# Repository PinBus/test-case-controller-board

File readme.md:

# Test-case Controller Board - Rev. 1.0

This board has been developed to control demo setups. It is essentially a smaller sized pinball machine controller. This board is based on the Arduino Uno, paired with a PCA9685 breakout board, eight MOSFETs and a four by four input matrix.

You will need to have a stencil made to make this board yourself. The SMD part footprints are not made for hand soldering.

**Warning: These designs are made as part of a hobby project and thus come with no guarantees. Do not use these designs in for any critical systems! Working with voltages higher than +40V can be potentially dangerous, please take appropriate safety measures!**

## Optional parts

 - Connectors **J2** and **J3** are optional. These headers expose the I2C bus and UART respectively.
 - Connectors **J4**, **J5**, and **J6** are optional. These headers expose the microcontroller pins.
 - Connector **J7** or **J8** are optional. These connectors are connected to the +5V rail. You will need at least one to power the board. The other connector can be used to power another board.
 - Connector **J9** or **J10** are optional. These connectors are connected to the +48V rail. You will need at least one when using the MOSFETs. The other connector can be used to power another board.
 - MOSFETs **Q1** thru **Q8** are optional:
   - Do not populate **R4**, **R6**, connector **SOL0**, and **D3** when not using **Q1**;
   - Do not populate **R8**, **R10**, connector **SOL1**, and **D4** when not using **Q2**;
   - Do not populate **R5**, **R7**, connector **SOL2**, and **D5** when not using **Q3**;
   - Do not populate **R9**, **R11**, connector **SOL3**, and **D6** when not using **Q4**;
   - Do not populate **R12**, **R14**, connector **SOL4**, and **D7** when not using **Q5**;
   - Do not populate **R16**, **R18**, connector **SOL5**, and **D8** when not using **Q6**;
   - Do not populate **R13**, **R15**, connector **SOL6**, and **D9** when not using **Q7**;
   - Do not populate **R17**, **R19**, connector **SOL7**, and **D10** when not using **Q8**;
 - When not using a MOSFET, you can use its pin on the PCA9685 to drive an LED:
   - Populate **LED0** if **Q1** is not used;
   - Populate **LED1** if **Q2** is not used;
   - Populate **LED2** if **Q3** is not used;
   - Populate **LED3** if **Q4** is not used;
   - Populate **LED4** if **Q5** is not used;
   - Populate **LED5** if **Q6** is not used;
   - Populate **LED6** if **Q7** is not used;
   - Populate **LED7** if **Q8** is not used;
 - **SOL0** and **SOL2** can be populated with either a 2 pin or a 3 pin connector:
   - Do not populate **SOL1** when **SOL0** is populated with a 3 pin connector;
   - Do not populate **SOL3** when **SOL2** is populated with a 3 pin connector;
 - All connectors and diodes making up the input matrix are optional:
   - Bridge **JP3** thru **JP6** to enable columns;
   - Bridge **JP7** thru **JP10** to enable rows;
 - Capacitors **C6** thru **C9** are optional. Populating **C6** is recommended. Populate others if needed.
 - Capacitors **C10** thru **C13** are optional. Populate if needed.

## BOM

| Identifiers                        | Quantity | Part number         | Manufacturer              | Footprint   | Description |
| ---------------------------------- | -------: | ------------------- | ------------------------- | ----------- | ----------- |
| C1                                 |       1x | CL10A475KQ8NNWC     | Samsung Electro-Mechanics | 0603        | Capacitor, MLCC, 4.7μF, 10V |
| C2, C3, C4, C5                     |       4x | GRM188R60J476ME15J  | Murata Electronics        | 0603        | Capacitor, MLCC, 47μF, 6.3V |
| C6, C7, C8, C9                     |       4x | URS1A470MDD1TA      | Nichicon                  | ⌀5mm / 2mm  | Capacitor, Electrolytic, 47μ, 10V |
| C10, C11, C12, C13                 |       4x | UVZ1J101MPD         | Nichicon                  | ⌀10mm / 5mm | Capacitor, Electrolytic, 100μF, 63V |
| C14                                |       1x | LMK107BBJ106MALT    | Taiyo Yuden               | 0603        | Capacitor, MLCC, 10μF, 10V |
| D1                                 |       1x | 150060RS75000       | Wurth Elektronik          | 0603        | LED, Red |
| D2                                 |       1x | 150060GS75000       | Wurth Elektronik          | 0603        | LED, Green |
| D3, D4, D5, D6, D7, D8, D9, D10    |       8x | S1M-13-F            | Diodes Incorporated       | SMA         | Diode, rectifier, 1A, 1000V |
| D11, D12, D13, D14, D15, D16, D17, D18, D19, D20, D21, D22, D23, D24, D25, D26 |      16x | 1N4148W-G3-08       | Vishay / Dale             | SOD-123     | Diode, general purpose, 150mA, 100V |
| J1                                 |       1x |                     |                           | 2.54mm      | Connector, 2x3, Pin header |
| J2, J3                             |       2x | B4B-XH-A(LF)(SN)    | JST                       | 2.50mm      | Connector, 1x4 |
| J4, J5                             |       2x |                     |                           | 2.54mm      | Connector, 1x8, pin header |
| J6                                 |       1x |                     |                           | 2.54mm      | Connector, 1x6, pin header |
| J7, J8, LED0, LED1, LED2, LED3, LED4, LED5, LED6, LED7, LED8, LED9, LED10, LED11, LED12, LED13, LED14, LED15, MTX-0x0, MTX-0x1, MTX-0x2, MTX-0x3, MTX-1x0, MTX-1x1, MTX-1x2, MTX-1x3, MTX-2x0, MTX-2x1, MTX-2x2, MTX-2x3, MTX-3x0, MTX-3x1, MTX-3x2, MTX-3x3 |      34x | B2B-XH-A(LF)(SN)    | JST                       | 2.50mm      | Connector, 1x2 |
| J9, J10, SOL0, SOL1, SOL2, SOL3, SOL4, SOL5, SOL6, SOL7 |      10x | B2P-VH _or_ 1-1123723-3 | JST _or_ TE Connectivity | 3.96mm      | Connector, 1x2 |
| JP1, JP2                           |       2x |                     |                           | 2.54mm      | Jumper wire |
| SOL0, SOL2                         |       2x | B3P-VH _or_ 1-1123723-2 | JST _or_ TE Connectivity | 3.96mm      | Connector, 1x3 |
| Q1, Q2, Q3, Q4, Q5, Q6, Q7, Q8     |       8x | IRL540NPBF          | Infineon / IR             | TO-220      | MOSFET, 100V, 36A |
| R1                                 |       1x | CRCW06034K70JNEAC   | Vishay / Dale             | 0603        | Resistor, 4.7kΩ |
| R2, R3                             |       2x | CRCW06031K00FKEAC   | Vishay / Dale             | 0603        | Resistor, 1kΩ |
| R4, R5, R8, R9, R12, R13, R16, R17 |       8x | CRCW060310R0FKEAC   | Vishay / Dale             | 0603        | Resistor, 10Ω |
| R6, R7, R10, R11, R14, R15, R18, R19, R20, R21, R22, R23, R24, R25, R26, R27, R28, R29, R30, R31, R32 |      21x | CRCW060310K0JNEAC   | Vishay / Dale             | 0603        | Resistor, 10kΩ |
| SW1                                |       1x | PTS810SJM250SMTRLFS | C&K                       | -           | Switch |
| U1                                 |       1x | ATmega328P-AU       | Microchip Technology      | TQFP-32     | Microcontroller |
| U2                                 |       1x | PCA9685PW,112       | NXP Semiconductors        | TSSOP-28    | PWM driver |
| Y1                                 |       1x | CSTNE16M0V53L00ZR0  | Murata Electronics        | -           | Resonator, 16MHz, 15pF |

### Pin headers

You can use either the [JST VH series](https://www.jst-mfg.com/product/detail_e.php?series=262) pin headers or the TE Connectivity Economy Power series pin headers. These pin headers are known to fit, other 3.96mm pin pitch pin headers might also fit.

 - Order the JST SVH-21T-P1.1 crimp contacts (0.34mm² - 0.75mm²) for use with the JST pin headers
 - Order JST VHR-2N connector housing for the JST B2P-VH pin header
 - Order JST VHR-3N connector housing for the JST B3P-VH pin header
 - Order the [TE Connectivity 1123721-2](https://www.te.com/usa-en/product-1123721-2.html) crimp contacts (0.34mm² - 0.75mm²) for use with the TE Connectivity pin headers
 - Order the [TE Connectivity 1-1123722-2](https://www.te.com/usa-en/product-1-1123722-2.html) connector housing for the [TE Connectivity 1-1123723-2](https://www.te.com/usa-en/product-1-1123723-2.html) pin header
 - Order the [TE Connectivity 1-1123722-3](https://www.te.com/usa-en/product-1-1123722-3.html) connector housing for the [TE Connectivity 1-1123723-3](https://www.te.com/usa-en/product-1-1123723-3.html) pin header

## Pictures

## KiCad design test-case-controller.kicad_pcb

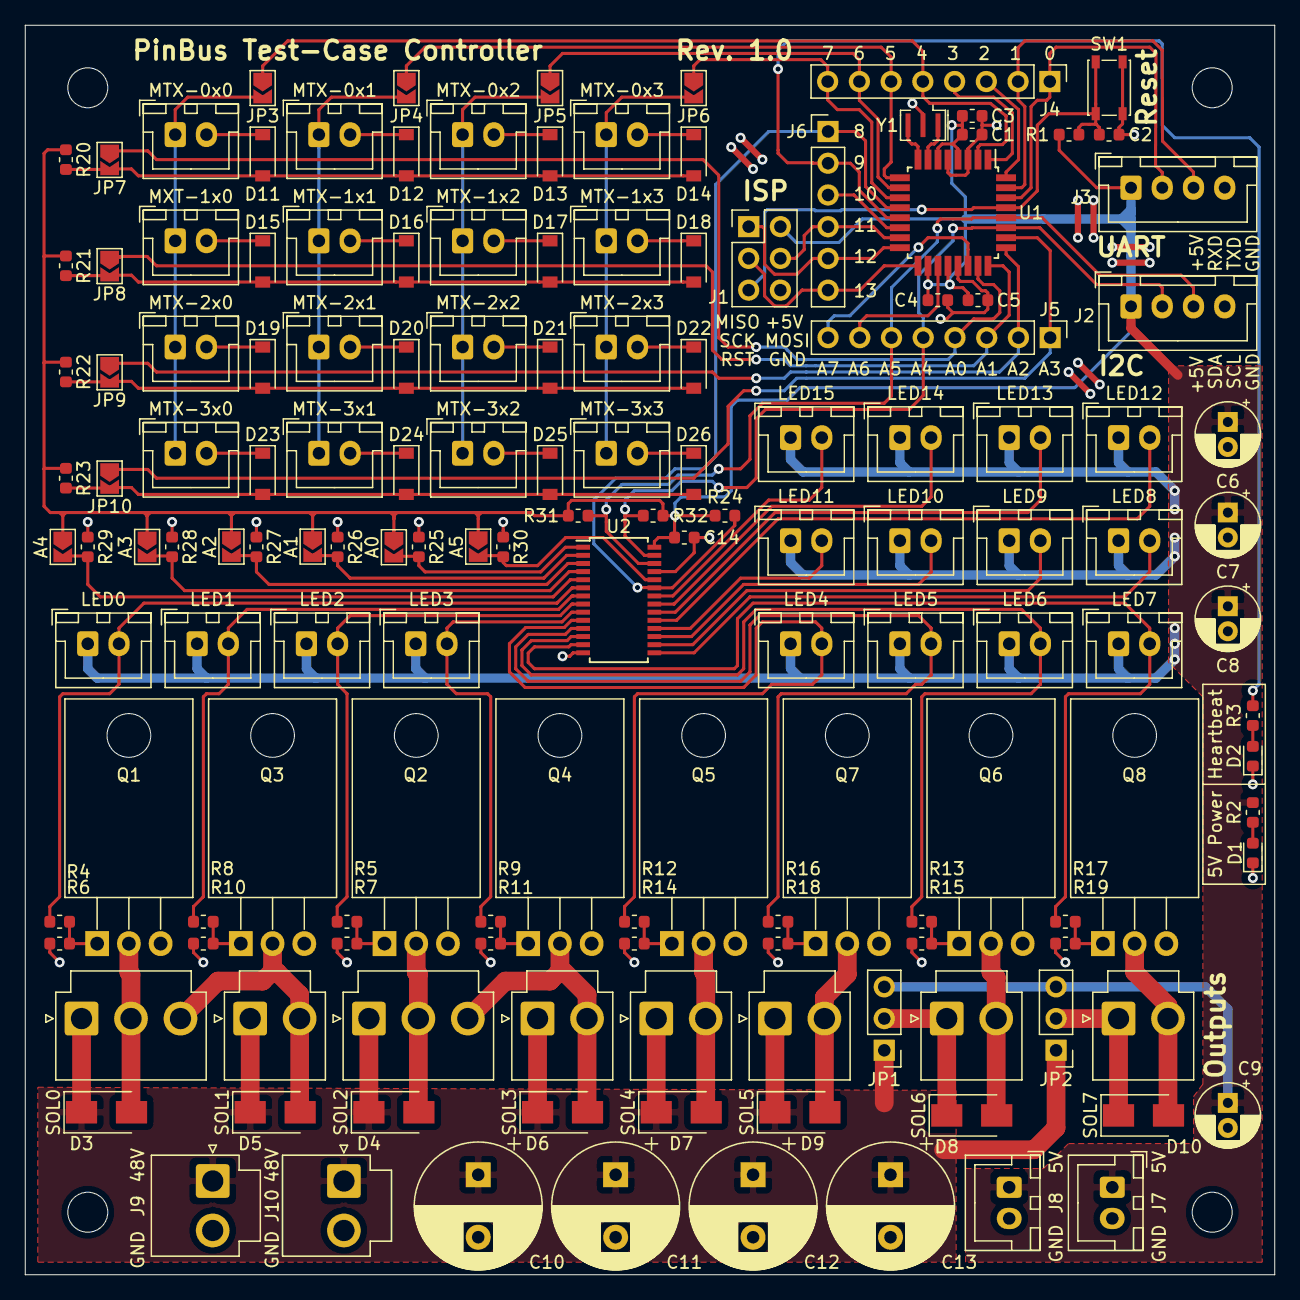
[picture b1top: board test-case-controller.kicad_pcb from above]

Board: 2 copper layers, 100.0 x 100.0 mm, 150 parts (0 on the bottom side), 94 nets.

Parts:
A0, A1, A2, A3, A4, A5: SolderJumper_2_Open; SolderJumper-2_P1.3mm_Open_TrianglePad1.0x1.5mm
C1: 4.7μF; C_0603_1608Metric
C2, C3, C4, C5: 100μF; C_0603_1608Metric
C6, C7, C8, C9: 47μF; CP_Radial_D5.0mm_P2.00mm
C10, C11, C12, C13: 100μF; CP_Radial_D10.0mm_P5.00mm
C14: 10μF; C_0603_1608Metric
D1, D2: LED; LED_0603_1608Metric
D3, D4, D5, D6, D7, D8, D9, D10: 1N4007; D_SMA
D11, D12, D13, D14, D15, D16, D17, D18, D19, D20, D21, D22, D23, D24, D25, D26: 1N4148W-G; D_SOD-123
J1: Pin Header 02x03; PinHeader_2x03_P2.54mm_Vertical
J2, J3: JST XH 01x04; JST_XH_B4B-XH-A_1x04_P2.50mm_Vertical
J4, J5: Pin header 01x08; PinHeader_1x08_P2.54mm_Vertical
J6: Pin header 01x06; PinHeader_1x06_P2.54mm_Vertical
J7, J8: JST XH 01x02; JST_XH_B2B-XH-A_1x02_P2.50mm_Vertical
J9, J10: JST VH 3.96 01x02; JST_VH_B2P-VH_1x02_P3.96mm_Vertical
JP1, JP2: Jumper_3_Open; PinHeader_1x03_P2.54mm_Vertical
JP3, JP4, JP5, JP6, JP7, JP8, JP9, JP10: SolderJumper_2_Open; SolderJumper-2_P1.3mm_Open_TrianglePad1.0x1.5mm
LED0, LED1, LED2, LED3, LED4, LED5, LED6, LED7: JST XH 2.50 01x02; JST_XH_B2B-XH-A_1x02_P2.50mm_Vertical
LED8, LED9, LED10, LED11, LED12, LED13, LED14, LED15: JST XH 01x02; JST_XH_B2B-XH-A_1x02_P2.50mm_Vertical
MTX-0x0, MTX-0x1, MTX-0x2, MTX-0x3, MTX-1x1, MTX-1x2, MTX-1x3, MTX-2x0, MTX-2x1, MTX-2x2, MTX-2x3, MTX-3x0, MTX-3x1, MTX-3x2, MTX-3x3: JST XH 2.50 01x02; JST_XH_B2B-XH-A_1x02_P2.50mm_Vertical
MXT-1x0: JST XH 2.50 01x02; JST_XH_B2B-XH-A_1x02_P2.50mm_Vertical
Q1, Q2, Q3, Q4, Q5, Q6, Q7, Q8: IRL540; TO-220-3_Horizontal_TabDown
R1: 4.7kΩ; R_0603_1608Metric
R2, R3: 1kΩ; R_0603_1608Metric
R4, R5, R8, R9, R12, R13, R16, R17: 10Ω; R_0603_1608Metric
R6, R7, R10, R11, R14, R15, R18, R19, R20, R21, R22, R23, R24, R25, R26, R27, R28, R29, R30, R31, R32: 10kΩ; R_0603_1608Metric
SOL0, SOL2: JST VH 3.96 01x03; JST_VH_B3P-VH_1x03_P3.96mm_Vertical
SOL1, SOL3, SOL4, SOL5, SOL6, SOL7: JST VH 3.96 01x02; JST_VH_B2P-VH_1x02_P3.96mm_Vertical
SW1: SW_Push; SW_SPST_PTS810
U1: ATmega328-AU; TQFP-32_7x7mm_P0.8mm
U2: PCA9685PW; TSSOP-28_4.4x9.7mm_P0.65mm
Y1: Resonator; Resonator_SMD_muRata_CSTxExxV-3Pin_3.0x1.1mm

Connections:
+5V: A0.1, A1.1, A2.1, A3.1, A4.1, A5.1, C1.1, C3.1, C4.2, C5.1, C6.1, C7.1, C8.1, C9.1, C14.1, J1.2, J2.1, J3.1, J7.1, J8.1, JP1.3, JP2.3, LED0.1, LED1.1, LED2.1, LED3.1, LED4.1, LED5.1, LED6.1, LED7.1, LED8.1, LED9.1, LED10.1, LED11.1, LED12.1, LED13.1, LED14.1, LED15.1, R1.1, R2.1, R20.1, R21.1, R22.1, R23.1, R24.2, R31.2, R32.2, U1.4, U1.6, U1.18, U1.20, U2.28
+48V: C10.1, C11.1, C12.1, C13.1, D3.1, D4.1, D5.1, D6.1, D7.1, D9.1, J9.1, J10.1, JP1.1, JP2.1, SOL0.1, SOL1.1, SOL2.1, SOL3.1, SOL4.1, SOL5.1
/Mainboard PCA9685/A0: A0.2, R25.2, U2.1
/Mainboard PCA9685/A1: A1.2, R26.2, U2.2
/Mainboard PCA9685/A2: A2.2, R27.2, U2.3
/Mainboard PCA9685/A3: A3.2, R28.2, U2.4
/Mainboard PCA9685/A4: A4.2, R29.2, U2.5
/Mainboard PCA9685/A5: A5.2, R30.2, U2.24
/Mainboard PCA9685/LED8: LED8.2, U2.15
/Mainboard PCA9685/LED9: LED9.2, U2.16
/Mainboard PCA9685/LED10: LED10.2, U2.17
/Mainboard PCA9685/LED11: LED11.2, U2.18
/Mainboard PCA9685/LED12: LED12.2, U2.19
/Mainboard PCA9685/LED13: LED13.2, U2.20
/Mainboard PCA9685/LED14: LED14.2, U2.21
/Mainboard PCA9685/LED15: LED15.2, U2.22
ADC6-A6: J5.7, U1.19
ADC7-A7: J5.8, U1.22
GND: C1.2, C2.2, C3.2, C4.1, C5.2, C6.2, C7.2, C8.2, C9.2, C10.2, C11.2, C12.2, C13.2, C14.2, D1.1, D2.1, J1.6, J2.4, J3.4, J7.2, J8.2, J9.2, J10.2, Q1.3, Q2.3, Q3.3, Q4.3, Q5.3, Q6.3, Q7.3, Q8.3, R6.2, R7.2, R10.2, R11.2, R14.2, R15.2, R18.2, R19.2, R25.1, R26.1, R27.1, R28.1, R29.1, R30.1, SW1.2, U1.3, U1.5, U1.21, U2.14, U2.25, Y1.2
LED0: LED0.2, R4.2, U2.6
LED1: LED1.2, R8.2, U2.7
LED2: LED2.2, R5.2, U2.8
LED3: LED3.2, R9.2, U2.9
LED4: LED4.2, R12.2, U2.10
LED5: LED5.2, R16.2, U2.11
LED6: LED6.2, R13.2, U2.12
LED7: LED7.2, R17.2, U2.13
unnamed: D1.2, R2.2
unnamed: D2.2, R3.2
unnamed: D3.2, Q1.2, SOL0.2
unnamed: D4.2, Q2.2, SOL2.2
unnamed: D5.2, Q3.2, SOL0.3, SOL1.2
unnamed: D6.2, Q4.2, SOL2.3, SOL3.2
unnamed: D7.2, Q5.2, SOL4.2
unnamed: D8.1, JP1.2, SOL6.1
unnamed: D8.2, Q6.2, SOL6.2
unnamed: D9.2, Q7.2, SOL5.2
unnamed: D10.1, JP2.2, SOL7.1
unnamed: D10.2, Q8.2, SOL7.2
unnamed: D11.1, MTX-0x0.2
unnamed: D11.2, D12.2, D13.2, D14.2, JP7.2, R20.2
unnamed: D12.1, MTX-0x1.2
unnamed: D13.1, MTX-0x2.2
unnamed: D14.1, MTX-0x3.2
unnamed: D15.1, MXT-1x0.2
unnamed: D15.2, D16.2, D17.2, D18.2, JP8.2, R21.2
unnamed: D16.1, MTX-1x1.2
unnamed: D17.1, MTX-1x2.2
unnamed: D18.1, MTX-1x3.2
unnamed: D19.1, MTX-2x0.2
unnamed: D19.2, D20.2, D21.2, D22.2, JP9.2, R22.2
unnamed: D20.1, MTX-2x1.2
unnamed: D21.1, MTX-2x2.2
unnamed: D22.1, MTX-2x3.2
unnamed: D23.1, MTX-3x0.2
unnamed: D23.2, D24.2, D25.2, D26.2, JP10.2, R23.2
unnamed: D24.1, MTX-3x1.2
unnamed: D25.1, MTX-3x2.2
unnamed: D26.1, MTX-3x3.2
unnamed: JP3.2, MTX-0x0.1, MTX-2x0.1, MTX-3x0.1, MXT-1x0.1
unnamed: JP4.2, MTX-0x1.1, MTX-1x1.1, MTX-2x1.1, MTX-3x1.1
unnamed: JP5.2, MTX-0x2.1, MTX-1x2.1, MTX-2x2.1, MTX-3x2.1
unnamed: JP6.2, MTX-0x3.1, MTX-1x3.1, MTX-2x3.1, MTX-3x3.1
unnamed: Q1.1, R4.1, R6.1
unnamed: Q2.1, R5.1, R7.1
unnamed: Q3.1, R8.1, R10.1
unnamed: Q4.1, R9.1, R11.1
unnamed: Q5.1, R12.1, R14.1
unnamed: Q6.1, R13.1, R15.1
unnamed: Q7.1, R16.1, R18.1
unnamed: Q8.1, R17.1, R19.1
PB0-08: J6.1, R24.1, U1.12, U2.23
PB1-09: J6.2, R3.1, U1.13
PB2-10-SS: J6.3, U1.14
PB3-11-MOSI: J1.4, J6.4, U1.15
PB4-12-MISO: J1.1, J6.5, U1.16
PB5-13-SCK: J1.3, J6.6, U1.17
PB6-xx-XTAL1: U1.7, Y1.1
PB7-xx-XTAL2: U1.8, Y1.3
PC0-A0: J5.4, JP7.1, U1.23
PC1-A1: J5.3, JP8.1, U1.24
PC2-A2: J5.2, JP9.1, U1.25
PC3-A3: J5.1, JP10.1, U1.26
PC4-A4-SDA: J2.2, J5.5, R32.1, U1.27, U2.27
PC5-A5-SCL: J2.3, J5.6, R31.1, U1.28, U2.26
PC6-xx-RESET: C2.1, J1.5, R1.2, SW1.1, U1.29
PD0-00-RXD: J3.2, J4.1, U1.30
PD1-01-TXD: J3.3, J4.2, U1.31
PD2-02-INT0: J4.3, U1.32
PD3-03-INT1: J4.4, U1.1
PD4-04: J4.5, JP3.1, U1.2
PD5-05: J4.6, JP4.1, U1.9
PD6-06: J4.7, JP5.1, U1.10
PD7-07: J4.8, JP6.1, U1.11

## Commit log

2021-07-09 Add board files
2021-07-09 Add notes on optional parts
2021-09-09 Add more information on power connectors and their alternatives
